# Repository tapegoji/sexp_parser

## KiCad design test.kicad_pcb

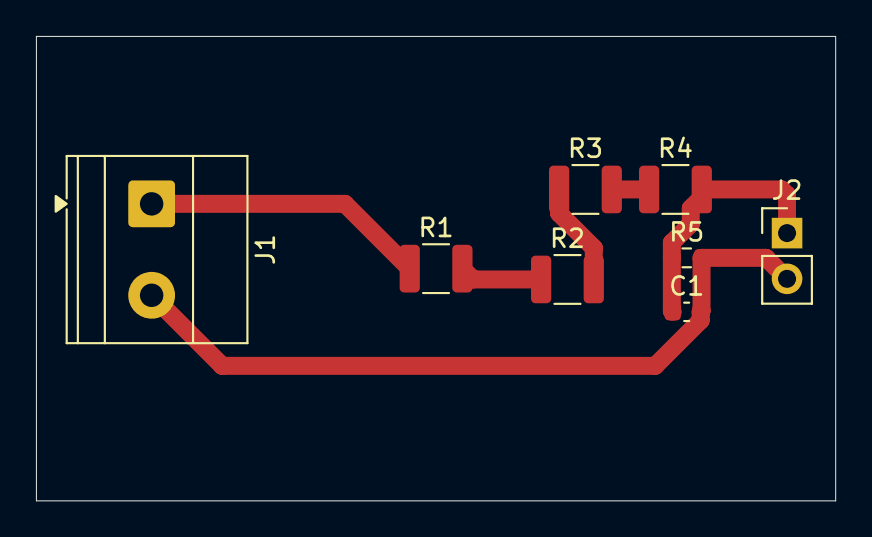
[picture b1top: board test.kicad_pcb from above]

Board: 2 copper layers, 44.4 x 25.8 mm, 8 parts (0 on the bottom side), 6 nets.

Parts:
C1: 1000 pF; C_0603_1608Metric
J1: Screw_Terminal_01x02; TerminalBlock_Phoenix_MKDS-1,5-2-5.08_1x02_P5.08mm_Horizont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
J2: Conn_01x02_Pin; PinHeader_1x02_P2.54mm_Vertical
R1, R2, R3, R4: 1 MOhms; R_1210_3225Metric
R5: 10 kOhms; R_0603_1608Metric

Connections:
GND: C1.2, J1.2, J2.2, R5.2
R2_P: R1.2, R2.1
R3_P: R2.2, R3.1
R4_P: R3.2, R4.1
VIN: J1.1, R1.1
VOUT: C1.1, J2.1, R4.2, R5.1

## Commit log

2025-06-10 conslidated maui's changes into fcad and made them a seperate repo
